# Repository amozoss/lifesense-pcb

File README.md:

lifesense-pcb
=============

Senior project hardware 

CC3000 lib/footprint obtained here: https://github.com/mcous/kicad-lib/

### Software
The pcb software can be found at [lifesense-pcb-software](https://github.com/amozoss/lifesense-pcb-software)

### Images

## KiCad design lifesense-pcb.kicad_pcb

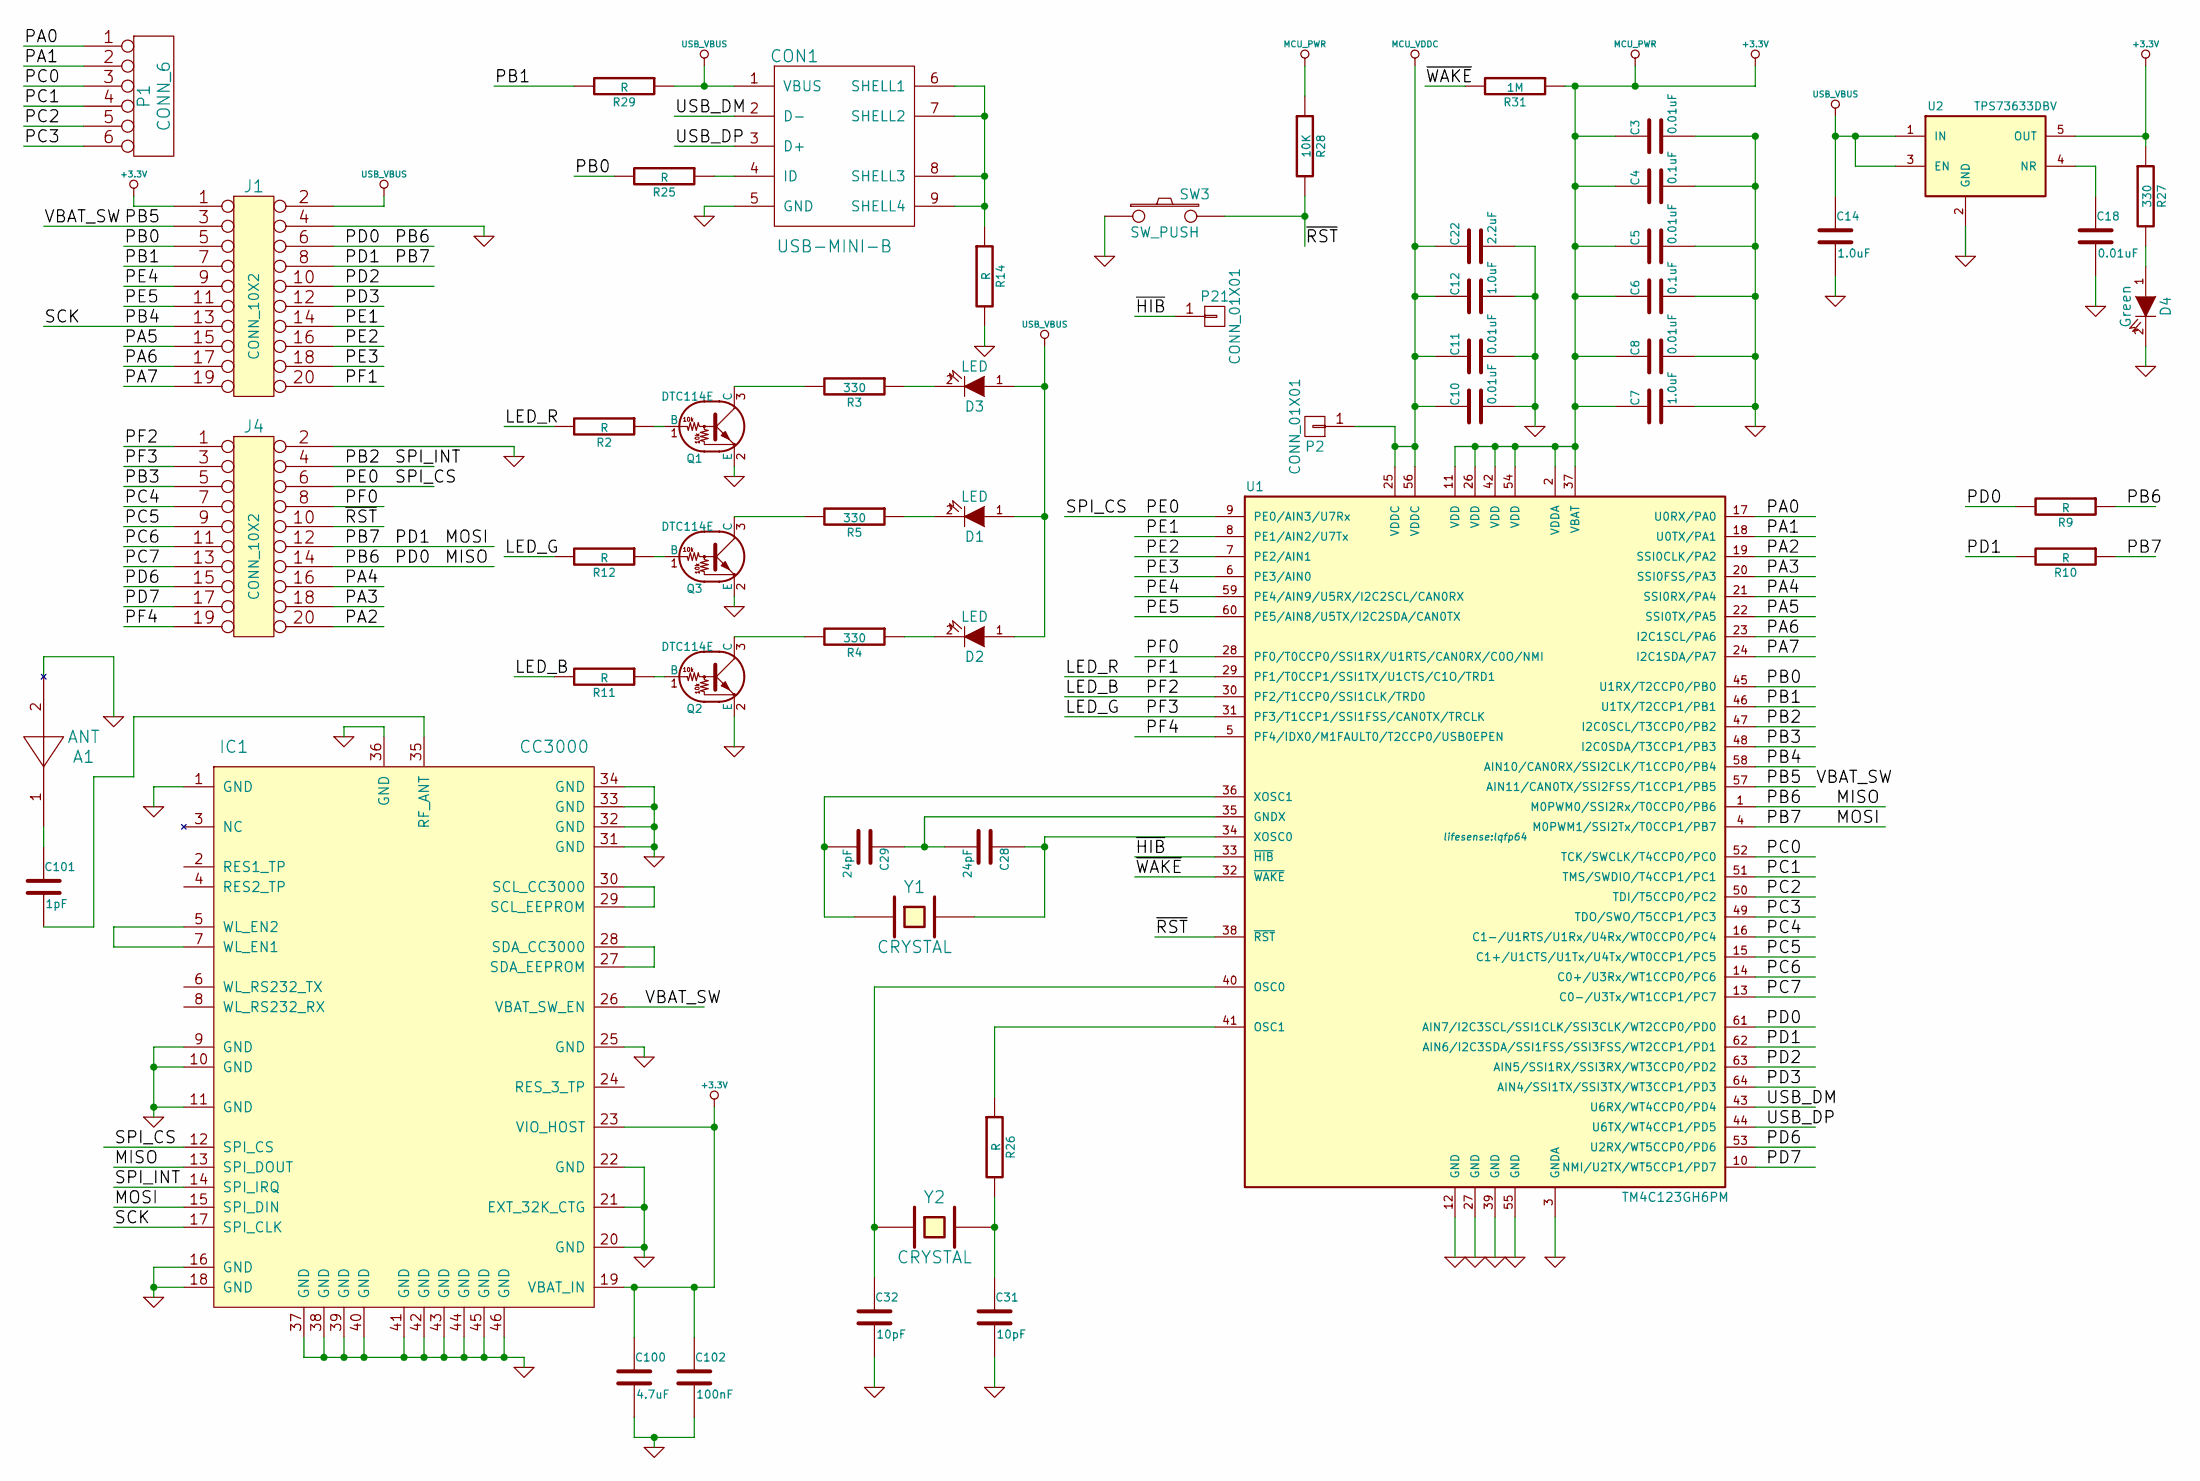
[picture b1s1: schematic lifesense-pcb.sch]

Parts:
A1: ANT; ant_Wigle_A2_4G
C3, C5, C8, C10, C11, C18: 0.01uF; SMD-0603_c
C4, C6: 0.1uF; SMD-0603_c
C7, C12, C14: 1.0uF; SMD-0603_c
C22: 2.2uF; SMD-0603_c
C28, C29: 24pF; SMD-0603_c
C31, C32: 10pF; SMD-0603_c
C100: 4.7uF; SMD-0603_c
C101: 1pF; SMD-0603_c
C102: 100nF; SMD-0603_c
CON1: USB-MINI-B; ZX62-AB-5PA(11)
D1, D2, D3: LED; LED-0805
D4: Green; LED-0805
IC1: CC3000; Manuf. Part CC3000MOD
J1, J4: CONN_10X2; Pin_Header_Straight_2x10
P1: CONN_6; Pin_Header_Straight_1x06
P2, P21: CONN_01X01; Pin_Header_Straight_1x01
Q1, Q2, Q3: DTC114E; DTC114EET1G
R2, R9, R10, R11, R12, R14, R25, R26, R29: R; SMD-0603_r
R3, R4, R5, R27: 330; SMD-0603_r
R28: 10K; SMD-0603_r
R31: 1M; SMD-0603_r
SW3: SW_PUSH
U1: TM4C123GH6PM; lqfp64
U2: TPS73633DBV
Y1: CRYSTAL; AB26TRB
Y2: CRYSTAL; ABM3

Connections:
/LED_B: J4.1, R11.2, U1.30 (PF2/T1CCP0/SSI1CLK/TRD0)
/LED_G: J4.3, R12.2, U1.31 (PF3/T1CCP1/SSI1FSS/CAN0TX/TRCLK)
/LED_R: J1.20, R2.2, U1.29 (PF1/T0CCP1/SSI1TX/U1CTS/C1O/TRD1)
/MISO: IC1.13 (SPI_DOUT), J1.6, J4.14, R9.1, R9.2, U1.1 (M0PWM0/SSI2Rx/T0CCP0/PB6), U1.61 (AIN7/I2C3SCL/SSI1CLK/SSI3CLK/WT2CCP0/PD0)
/MOSI: IC1.15 (SPI_DIN), J1.8, J4.12, R10.1, R10.2, U1.4 (M0PWM1/SSI2Tx/T0CCP1/PB7), U1.62 (AIN6/I2C3SDA/SSI1FSS/SSI3FSS/WT2CCP1/PD1)
/PA0: P1.1, U1.17 (U0RX/PA0)
/PA1: P1.2, U1.18 (U0TX/PA1)
/PA2: J4.20, U1.19 (SSI0CLK/PA2)
/PA3: J4.18, U1.20 (SSI0FSS/PA3)
/PA4: J4.16, U1.21 (SSI0RX/PA4)
/PA5: J1.15, U1.22 (SSI0TX/PA5)
/PA6: J1.17, U1.23 (I2C1SCL/PA6)
/PA7: J1.19, U1.24 (I2C1SDA/PA7)
/PB0: J1.5, R25.2, U1.45 (U1RX/T2CCP0/PB0)
/PB1: J1.7, R29.2, U1.46 (U1TX/T2CCP1/PB1)
/PB2: IC1.14 (SPI_IRQ), J4.4, U1.47 (I2C0SCL/T3CCP0/PB2)
/PB3: J4.5, U1.48 (I2C0SDA/T3CCP1/PB3)
/PB4: IC1.17 (SPI_CLK), J1.13, U1.58 (AIN10/CAN0RX/SSI2CLK/T1CCP0/PB4)
/PB5: IC1.26 (VBAT_SW_EN), J1.3, U1.57 (AIN11/CAN0TX/SSI2FSS/T1CCP1/PB5)
/PC0: P1.3, U1.52 (TCK/SWCLK/T4CCP0/PC0)
/PC1: P1.4, U1.51 (TMS/SWDIO/T4CCP1/PC1)
/PC2: P1.5, U1.50 (TDI/T5CCP0/PC2)
/PC3: P1.6, U1.49 (TDO/SWO/T5CCP1/PC3)
/PC4: J4.7, U1.16 (C1-/U1RTS/U1Rx/U4Rx/WT0CCP0/PC4)
/PC5: J4.9, U1.15 (C1+/U1CTS/U1Tx/U4Tx/WT0CCP1/PC5)
/PC6: J4.11, U1.14 (C0+/U3Rx/WT1CCP0/PC6)
/PC7: J4.13, U1.13 (C0-/U3Tx/WT1CCP1/PC7)
/PD2: J1.10, U1.63 (AIN5/SSI1RX/SSI3RX/WT3CCP0/PD2)
/PD3: J1.12, U1.64 (AIN4/SSI1TX/SSI3TX/WT3CCP1/PD3)
/PD6: J4.15, U1.53 (U2RX/WT5CCP0/PD6)
/PD7: J4.17, U1.10 (NMI/U2TX/WT5CCP1/PD7)
/PE0: IC1.12 (SPI_CS), J4.6, U1.9 (PE0/AIN3/U7Rx)
/PE1: J1.14, U1.8 (PE1/AIN2/U7Tx)
/PE2: J1.16, U1.7 (PE2/AIN1)
/PE3: J1.18, U1.6 (PE3/AIN0)
/PE4: J1.9, U1.59 (PE4/AIN9/U5RX/I2C2SCL/CAN0RX)
/PE5: J1.11, U1.60 (PE5/AIN8/U5TX/I2C2SDA/CAN0TX)
/PF0: J4.8, U1.28 (PF0/T0CCP0/SSI1RX/U1RTS/CAN0RX/C0O/NMI)
/PF4: J4.19, U1.5 (PF4/IDX0/M1FAULT0/T2CCP0/USB0EPEN)
/USB_DM: CON1.2 (D-), U1.43 (U6RX/WT4CCP0/PD4)
/USB_DP: CON1.3 (D+), U1.44 (U6TX/WT4CCP1/PD5)
/~HIB~: P21.1, U1.33 (~HIB~)
/~RST~: J4.10, R28.2, SW3.2, U1.38 (~RST~)
/~WAKE~: R31.2, U1.32 (~WAKE~)
GND: A1.2, C3.2, C4.2, C5.2, C6.2, C7.2, C8.2, C10.2, C11.2, C12.2, C14.2, C18.2, C22.2, C31.2, C32.2, C100.2, C102.2, CON1.5 (GND), D4.2 (K), IC1.1 (GND), IC1.9 (GND), IC1.10 (GND), IC1.11 (GND), IC1.16 (GND), IC1.18 (GND), IC1.20 (GND), IC1.21 (EXT_32K_CTG), IC1.22 (GND), IC1.25 (GND), IC1.31 (GND), IC1.32 (GND), IC1.33 (GND), IC1.34 (GND), IC1.36 (GND), IC1.37 (GND), IC1.38 (GND), IC1.39 (GND), IC1.40 (GND), IC1.41 (GND), IC1.42 (GND), IC1.43 (GND), IC1.44 (GND), IC1.45 (GND), IC1.46 (GND), J1.4, J4.2, Q1.2 (E), Q2.2 (E), Q3.2 (E), R14.2, SW3.1, U1.3 (GNDA), U1.12 (GND), U1.27 (GND), U1.39 (GND), U1.55 (GND), U2.2 (GND)
MCU_PWR: C3.1, C4.1, C5.1, C6.1, C7.1, C8.1, C100.1, C102.1, IC1.19 (VBAT_IN), IC1.23 (VIO_HOST), J1.1, R27.1, R28.1, R31.1, U1.2 (VDDA), U1.11 (VDD), U1.26 (VDD), U1.37 (VBAT), U1.42 (VDD), U1.54 (VDD), U2.5 (OUT)
MCU_VDDC: C10.1, C11.1, C12.1, C22.1, P2.1, U1.25 (VDDC), U1.56 (VDDC)
unnamed: A1.1, C101.1
unnamed: C18.1, U2.4 (NR)
unnamed: C28.1, U1.34 (XOSC0), Y1.2
unnamed: C28.2, C29.1, U1.35 (GNDX)
unnamed: C29.2, U1.36 (XOSC1), Y1.1
unnamed: C31.1, R26.2, Y2.2
unnamed: C32.1, U1.40 (OSC0), Y2.1
unnamed: C101.2, IC1.35 (RF_ANT)
unnamed: CON1.4 (ID), R25.1
unnamed: CON1.6 (SHELL1), CON1.7 (SHELL2), CON1.8 (SHELL3), CON1.9 (SHELL4), R14.1
unnamed: D1.2 (K), R5.1
unnamed: D2.2 (K), R4.1
unnamed: D3.2 (K), R3.1
unnamed: D4.1 (A), R27.2
unnamed: IC1.5 (WL_EN2), IC1.7 (WL_EN1)
unnamed: IC1.27 (SDA_EEPROM), IC1.28 (SDA_CC3000)
unnamed: IC1.29 (SCL_EEPROM), IC1.30 (SCL_CC3000)
unnamed: Q1.1 (B), R2.1
unnamed: Q1.3 (C), R3.2
unnamed: Q2.1 (B), R11.1
unnamed: Q2.3 (C), R4.2
unnamed: Q3.1 (B), R12.1
unnamed: Q3.3 (C), R5.2
unnamed: R26.1, U1.41 (OSC1)
USB_VBUS: C14.1, CON1.1 (VBUS), D1.1 (A), D2.1 (A), D3.1 (A), J1.2, R29.1, U2.1 (IN), U2.3 (EN)

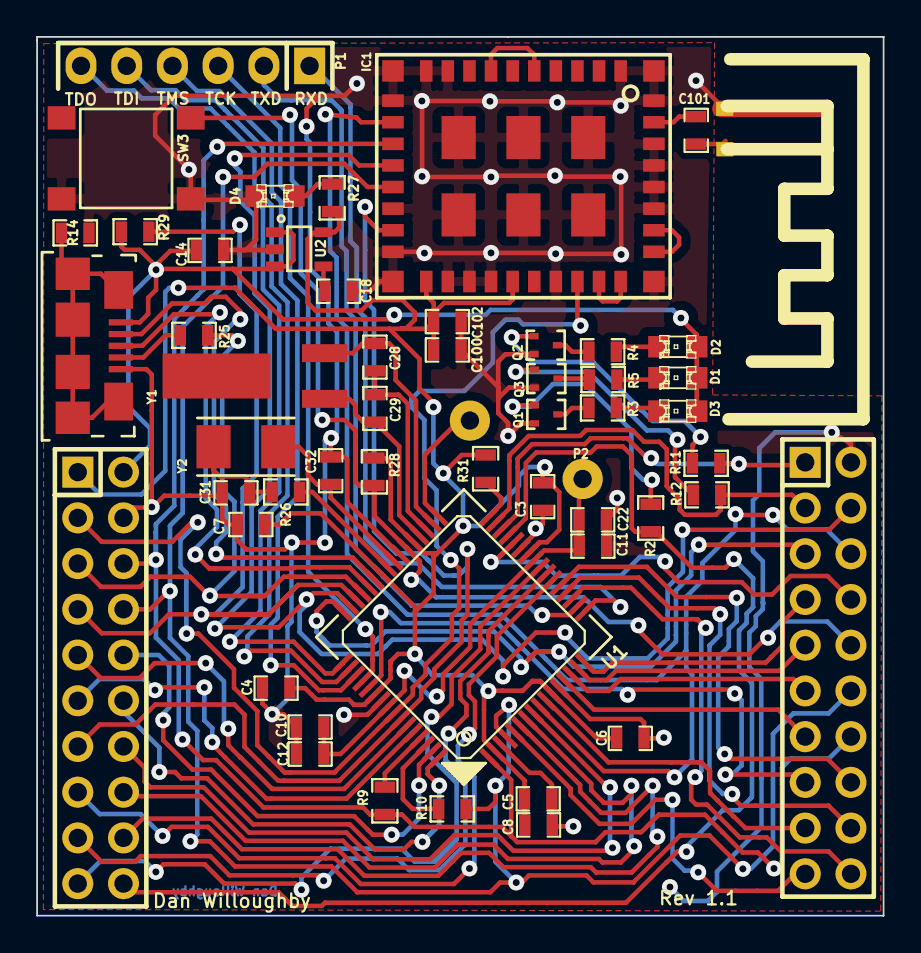
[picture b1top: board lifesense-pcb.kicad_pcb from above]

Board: 2 copper layers, 47.0 x 48.8 mm, 54 parts (0 on the bottom side), 72 nets.

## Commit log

2014-05-31 added resistor
2014-05-31 zach ssh key test. Updated README
2014-06-09 Adding msp430 and cc3000 footprint.
2014-06-12 moving to tiva-c TM4C123GH6PM chip
2014-08-29 only 2 things wrong, missing button
2014-09-12 finished board 1.0
2014-12-13 fabricated 1.1 version
2014-12-29 Create LICENSE
2014-12-29 add some images
